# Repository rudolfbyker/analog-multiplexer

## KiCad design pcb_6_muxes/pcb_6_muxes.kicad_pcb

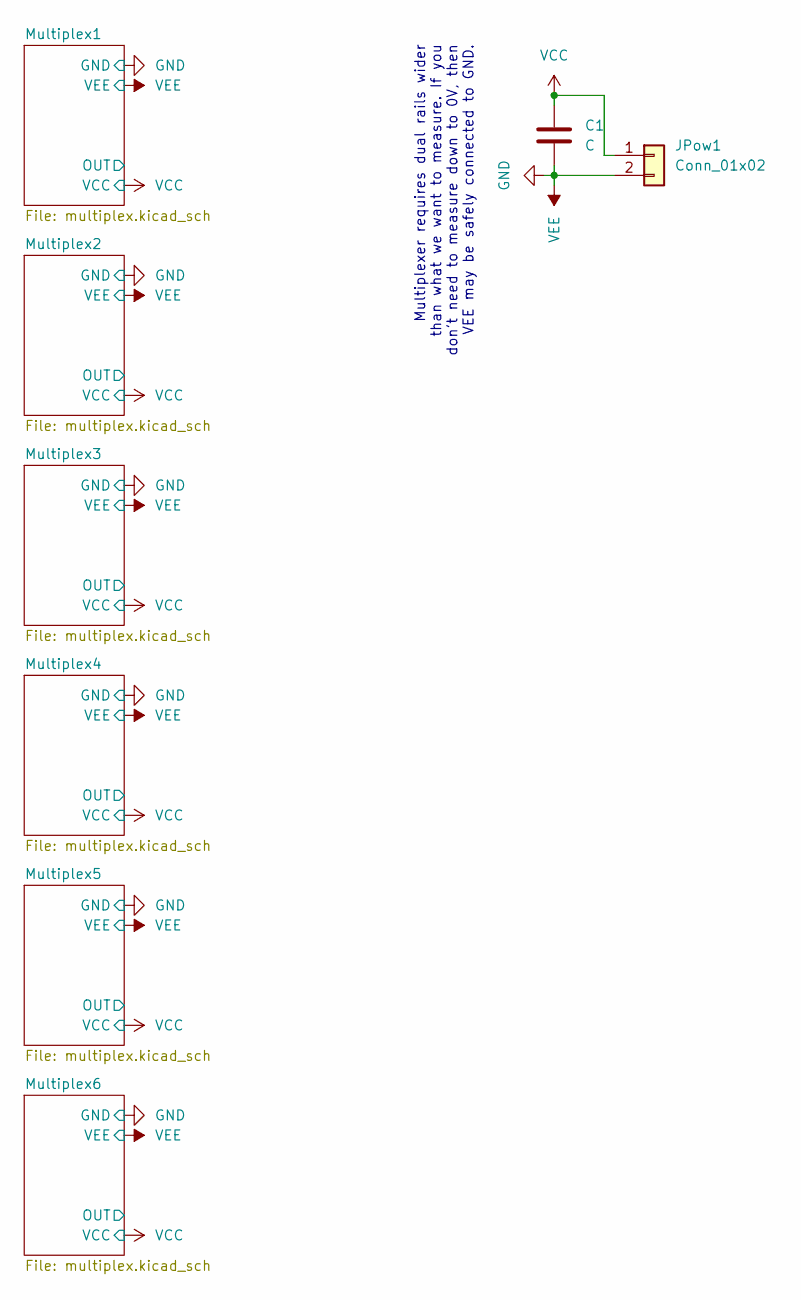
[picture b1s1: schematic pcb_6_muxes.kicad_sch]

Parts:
C1: C; C_Radial_D6.3mm_H5.0mm_P2.50mm
JPow1: Conn_01x02; PinHeader_1x02_P2.54mm_Vertical

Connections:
GND: C1.2, JPow1.2; also elsewhere on the board
VCC: C1.1, JPow1.1; also elsewhere on the board

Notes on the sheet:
Multiplexer requires dual rails wider than what we want to measure. If you don't need to measure down to 0V, then VEE may be safely connected to GND.

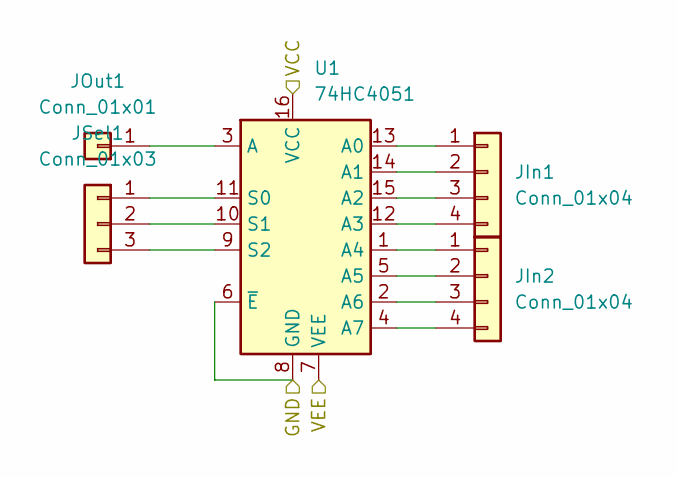
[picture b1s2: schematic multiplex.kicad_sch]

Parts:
JIn1, JIn2: Conn_01x04; PinHeader_1x04_P2.54mm_Vertical
JOut1: Conn_01x01; PinHeader_1x01_P2.54mm_Vertical
JSel1: Conn_01x03; PinHeader_1x03_P2.54mm_Vertical
U1: 74HC4051; DIP-16_W12.7mm_LongPads

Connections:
GND: U1.6 (~E), U1.7 (VEE), U1.8 (GND); also elsewhere on the board
unnamed: JIn1.1, U1.13 (A0)
unnamed: JIn1.2, U1.14 (A1)
unnamed: JIn1.3, U1.15 (A2)
unnamed: JIn1.4, U1.12 (A3)
unnamed: JIn2.1, U1.1 (A4)
unnamed: JIn2.2, U1.5 (A5)
unnamed: JIn2.3, U1.2 (A6)
unnamed: JIn2.4, U1.4 (A7)
unnamed: JOut1.1, U1.3 (A)
unnamed: JSel1.1, U1.11 (S0)
unnamed: JSel1.2, U1.10 (S1)
unnamed: JSel1.3, U1.9 (S2)
VCC: U1.16 (VCC); also elsewhere on the board

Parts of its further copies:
JIn3, JIn4, JIn5, JIn6, JIn7, JIn8, JIn9, JIn10, JIn11, JIn12: Conn_01x04; PinHeader_1x04_P2.54mm_Vertical
JOut2, JOut3, JOut4, JOut5, JOut6: Conn_01x01; PinHeader_1x01_P2.54mm_Vertical
JSel2, JSel3, JSel4, JSel5, JSel6: Conn_01x03; PinHeader_1x03_P2.54mm_Vertical
U2, U3, U4, U5, U6: 74HC4051; DIP-16_W12.7mm_LongPads

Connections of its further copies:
GND: U2.6 (~E), U2.7 (VEE), U2.8 (GND), U3.6 (~E), U3.7 (VEE), U3.8 (GND), U4.6 (~E), U4.7 (VEE), U4.8 (GND), U5.6 (~E), U5.7 (VEE), U5.8 (GND), U6.6 (~E), U6.7 (VEE), U6.8 (GND); also elsewhere on the board
unnamed: JIn3.1, U2.13 (A0)
unnamed: JIn3.2, U2.14 (A1)
unnamed: JIn3.3, U2.15 (A2)
unnamed: JIn3.4, U2.12 (A3)
unnamed: JIn4.1, U2.1 (A4)
unnamed: JIn4.2, U2.5 (A5)
unnamed: JIn4.3, U2.2 (A6)
unnamed: JIn4.4, U2.4 (A7)
unnamed: JIn5.1, U3.13 (A0)
unnamed: JIn5.2, U3.14 (A1)
unnamed: JIn5.3, U3.15 (A2)
unnamed: JIn5.4, U3.12 (A3)
unnamed: JIn6.1, U3.1 (A4)
unnamed: JIn6.2, U3.5 (A5)
unnamed: JIn6.3, U3.2 (A6)
unnamed: JIn6.4, U3.4 (A7)
unnamed: JIn7.1, U4.13 (A0)
unnamed: JIn7.2, U4.14 (A1)
unnamed: JIn7.3, U4.15 (A2)
unnamed: JIn7.4, U4.12 (A3)
unnamed: JIn8.1, U4.1 (A4)
unnamed: JIn8.2, U4.5 (A5)
unnamed: JIn8.3, U4.2 (A6)
unnamed: JIn8.4, U4.4 (A7)
unnamed: JIn9.1, U5.13 (A0)
unnamed: JIn9.2, U5.14 (A1)
unnamed: JIn9.3, U5.15 (A2)
unnamed: JIn9.4, U5.12 (A3)
unnamed: JIn10.1, U5.1 (A4)
unnamed: JIn10.2, U5.5 (A5)
unnamed: JIn10.3, U5.2 (A6)
unnamed: JIn10.4, U5.4 (A7)
unnamed: JIn11.1, U6.13 (A0)
unnamed: JIn11.2, U6.14 (A1)
unnamed: JIn11.3, U6.15 (A2)
unnamed: JIn11.4, U6.12 (A3)
unnamed: JIn12.1, U6.1 (A4)
unnamed: JIn12.2, U6.5 (A5)
unnamed: JIn12.3, U6.2 (A6)
unnamed: JIn12.4, U6.4 (A7)
unnamed: JOut2.1, U2.3 (A)
unnamed: JOut3.1, U3.3 (A)
unnamed: JOut4.1, U4.3 (A)
unnamed: JOut5.1, U5.3 (A)
unnamed: JOut6.1, U6.3 (A)
unnamed: JSel2.1, U2.11 (S0)
unnamed: JSel2.2, U2.10 (S1)
unnamed: JSel2.3, U2.9 (S2)
unnamed: JSel3.1, U3.11 (S0)
unnamed: JSel3.2, U3.10 (S1)
unnamed: JSel3.3, U3.9 (S2)
unnamed: JSel4.1, U4.11 (S0)
unnamed: JSel4.2, U4.10 (S1)
unnamed: JSel4.3, U4.9 (S2)
unnamed: JSel5.1, U5.11 (S0)
unnamed: JSel5.2, U5.10 (S1)
unnamed: JSel5.3, U5.9 (S2)
unnamed: JSel6.1, U6.11 (S0)
unnamed: JSel6.2, U6.10 (S1)
unnamed: JSel6.3, U6.9 (S2)
VCC: U2.16 (VCC), U3.16 (VCC), U4.16 (VCC), U5.16 (VCC), U6.16 (VCC); also elsewhere on the board

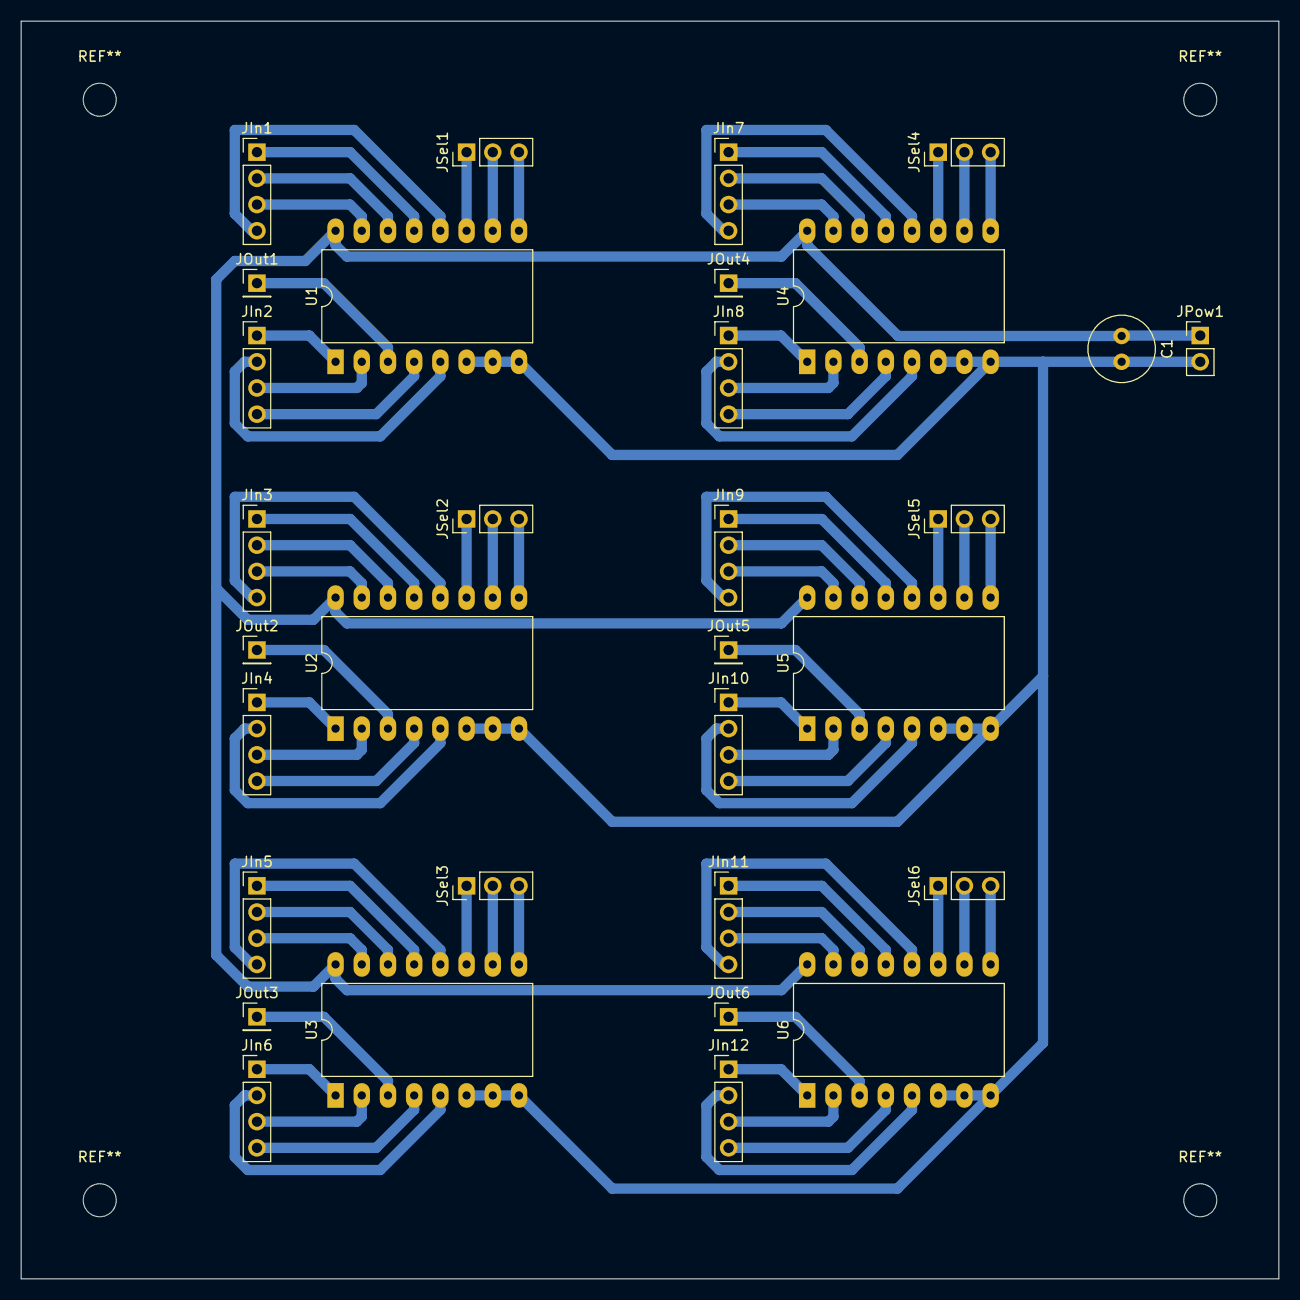
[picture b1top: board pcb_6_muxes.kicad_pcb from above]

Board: 2 copper layers, 121.9 x 121.9 mm, 32 parts (0 on the bottom side), 74 nets.

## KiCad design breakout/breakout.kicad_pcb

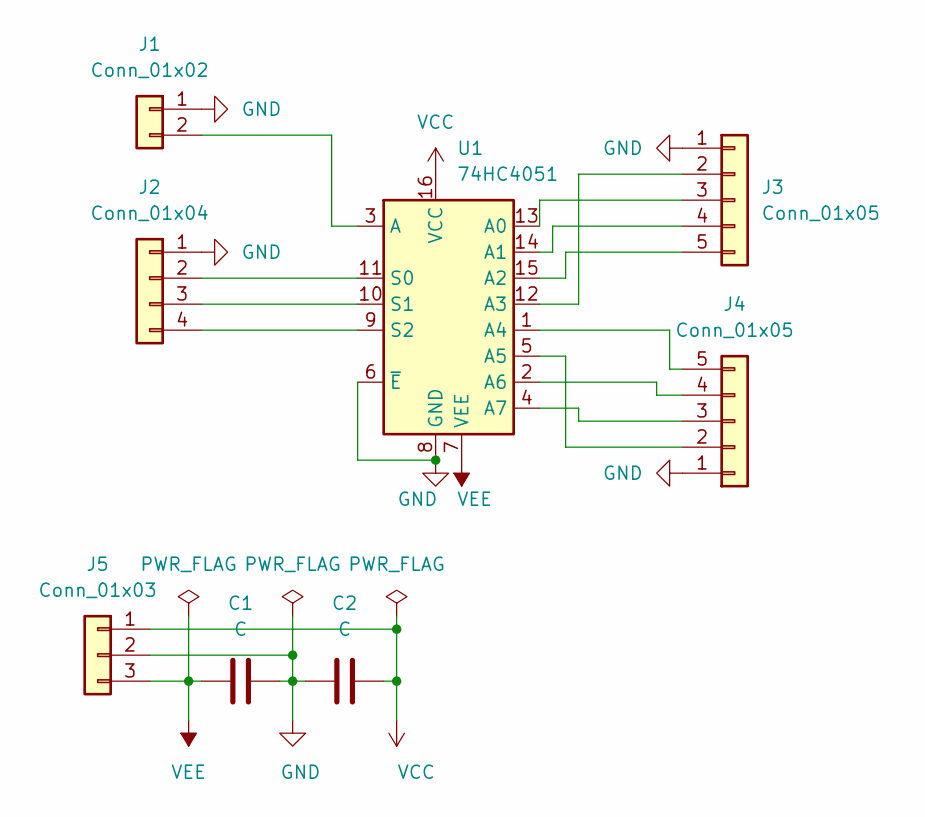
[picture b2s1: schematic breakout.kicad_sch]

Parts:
C1, C2: C; C_0805_2012Metric_Pad1.18x1.45mm_HandSolder
J1: Conn_01x02; PinHeader_1x02_P2.54mm_Vertical
J2: Conn_01x04; PinHeader_1x04_P2.54mm_Vertical
J3, J4: Conn_01x05; PinHeader_1x05_P2.54mm_Vertical
J5: Conn_01x03; PinHeader_1x03_P2.54mm_Vertical
U1: 74HC4051; SO-16_5.3x10.2mm_P1.27mm

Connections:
GND: C1.2, C2.1, J1.1, J2.1, J3.1, J4.1, J5.2, U1.6 (~E), U1.8 (GND)
unnamed: J1.2, U1.3 (A)
unnamed: J2.2, U1.11 (S0)
unnamed: J2.3, U1.10 (S1)
unnamed: J2.4, U1.9 (S2)
unnamed: J3.2, U1.12 (A3)
unnamed: J3.3, U1.13 (A0)
unnamed: J3.4, U1.14 (A1)
unnamed: J3.5, U1.15 (A2)
unnamed: J4.2, U1.5 (A5)
unnamed: J4.3, U1.4 (A7)
unnamed: J4.4, U1.2 (A6)
unnamed: J4.5, U1.1 (A4)
VCC: C2.2, J5.1, U1.16 (VCC)
VEE: C1.1, J5.3, U1.7 (VEE)

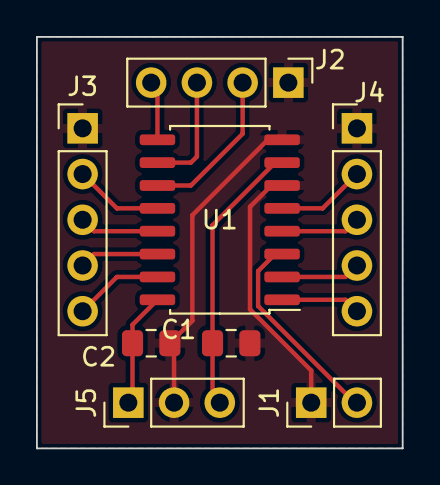
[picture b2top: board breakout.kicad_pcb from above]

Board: 2 copper layers, 20.3 x 22.9 mm, 8 parts (0 on the bottom side), 15 nets.

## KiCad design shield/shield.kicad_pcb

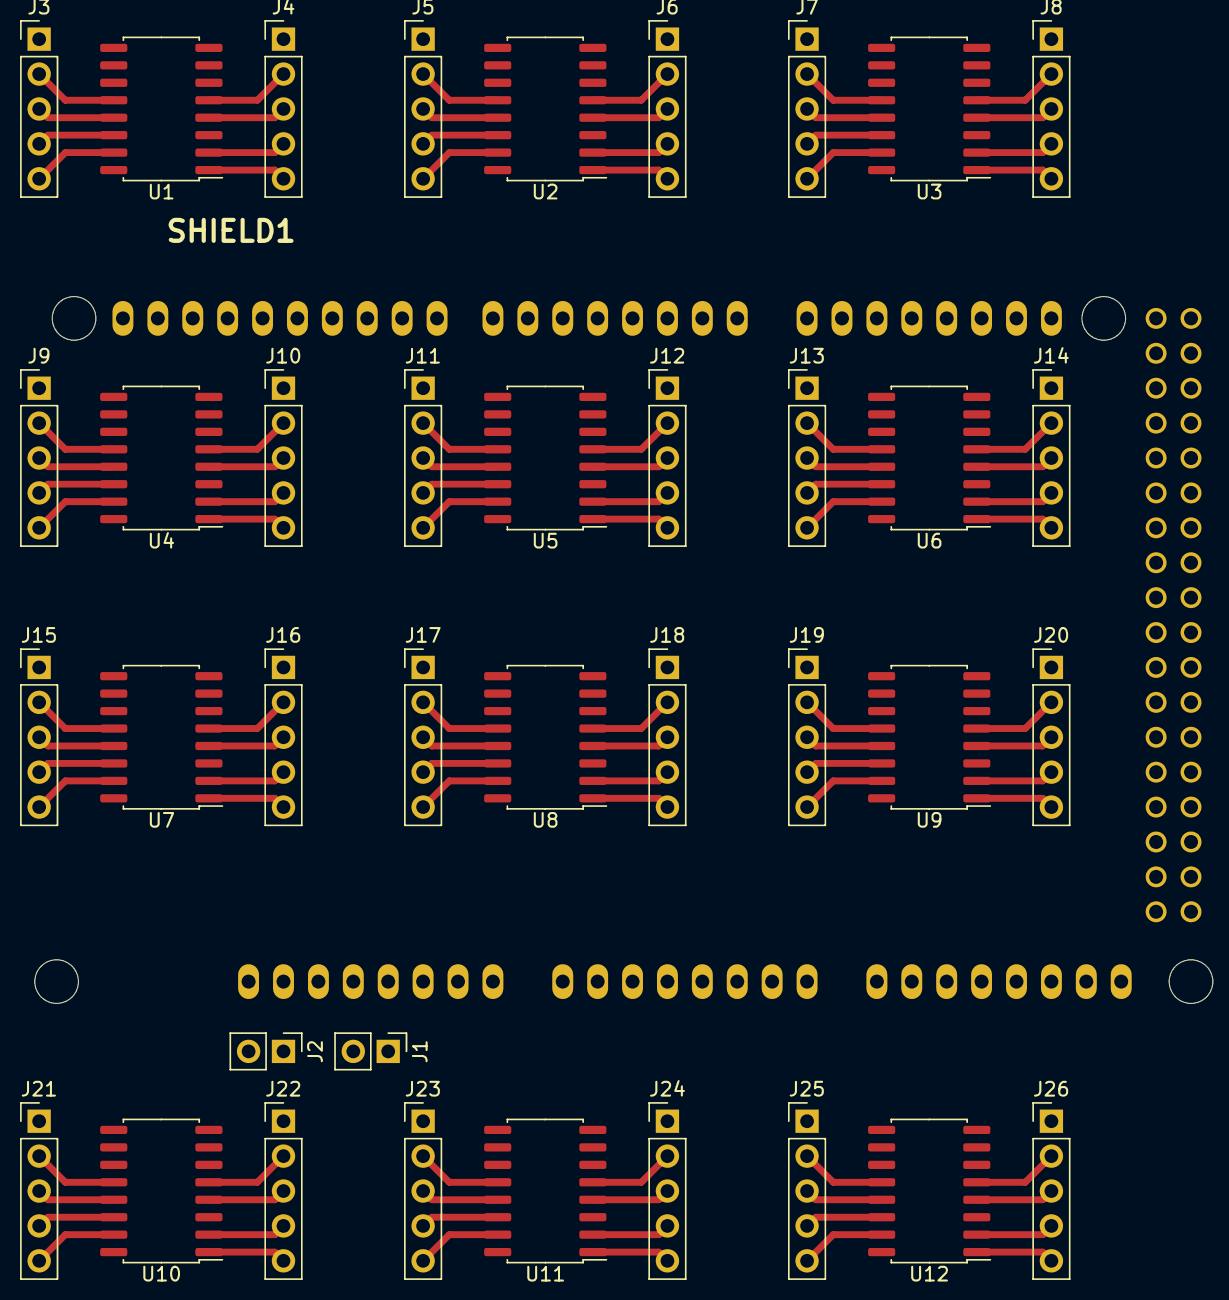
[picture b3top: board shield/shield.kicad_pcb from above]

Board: 2 copper layers, 39 parts (0 on the bottom side), 112 nets.

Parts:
J1, J2: Conn_01x02; PinHeader_1x02_P2.54mm_Vertical
J3, J4, J5, J6, J7, J8, J9, J10, J11, J12, J13, J14, J15, J16, J17, J18, J19, J20, J21, J22, J23, J24, J25, J26: Conn_01x05; PinHeader_1x05_P2.54mm_Vertical
SHIELD1: ARDUINO_DUE_SHIELD
U1, U2, U3, U4, U5, U6, U7, U8, U9, U10, U11, U12: 74HC4051; SO-16_5.3x10.2mm_P1.27mm

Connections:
+3V3: J1.2, SHIELD1.3V3
/A0: SHIELD1.AD0, U1.3 (A)
/A1: SHIELD1.AD1, U2.3 (A)
/A2: SHIELD1.AD2, U3.3 (A)
/A3: SHIELD1.AD3, U4.3 (A)
/A4: SHIELD1.AD4, U5.3 (A)
/A5: SHIELD1.AD5, U6.3 (A)
/A6: SHIELD1.AD6, U7.3 (A)
/A7: SHIELD1.AD7, U8.3 (A)
/A8: SHIELD1.AD8, U9.3 (A)
/A9: SHIELD1.AD9, U10.3 (A)
/A10: SHIELD1.AD10, U11.3 (A)
/A11: SHIELD1.AD11, U12.3 (A)
GND: J1.1, J2.1, J3.1, J4.1, J5.1, J6.1, J7.1, J8.1, J9.1, J10.1, J11.1, J12.1, J13.1, J14.1, J15.1, J16.1, J17.1, J18.1, J19.1, J20.1, J21.1, J22.1, J23.1, J24.1, J25.1, J26.1, SHIELD1.GND1, U1.6 (~E), U1.8 (GND), U2.6 (~E), U2.8 (GND), U3.6 (~E), U3.8 (GND), U4.6 (~E), U4.8 (GND), U5.6 (~E), U5.8 (GND), U6.6 (~E), U6.8 (GND), U7.6 (~E), U7.8 (GND), U8.6 (~E), U8.8 (GND), U9.6 (~E), U9.8 (GND), U10.6 (~E), U10.8 (GND), U11.6 (~E), U11.8 (GND), U12.6 (~E), U12.8 (GND)
unnamed: J4.5, U1.1 (A4)
unnamed: J4.4, U1.2 (A6)
unnamed: J4.3, U1.4 (A7)
unnamed: J4.2, U1.5 (A5)
unnamed: J3.2, U1.12 (A3)
unnamed: J3.3, U1.13 (A0)
unnamed: J3.4, U1.14 (A1)
unnamed: J3.5, U1.15 (A2)
unnamed: J6.5, U2.1 (A4)
unnamed: J6.4, U2.2 (A6)
unnamed: J6.3, U2.4 (A7)
unnamed: J6.2, U2.5 (A5)
unnamed: J5.2, U2.12 (A3)
unnamed: J5.3, U2.13 (A0)
unnamed: J5.4, U2.14 (A1)
unnamed: J5.5, U2.15 (A2)
unnamed: J8.5, U3.1 (A4)
unnamed: J8.4, U3.2 (A6)
unnamed: J8.3, U3.4 (A7)
unnamed: J8.2, U3.5 (A5)
unnamed: J7.2, U3.12 (A3)
unnamed: J7.3, U3.13 (A0)
unnamed: J7.4, U3.14 (A1)
unnamed: J7.5, U3.15 (A2)
unnamed: J10.5, U4.1 (A4)
unnamed: J10.4, U4.2 (A6)
unnamed: J10.3, U4.4 (A7)
unnamed: J10.2, U4.5 (A5)
unnamed: J9.2, U4.12 (A3)
unnamed: J9.3, U4.13 (A0)
unnamed: J9.4, U4.14 (A1)
unnamed: J9.5, U4.15 (A2)
unnamed: J12.5, U5.1 (A4)
unnamed: J12.4, U5.2 (A6)
unnamed: J12.3, U5.4 (A7)
unnamed: J12.2, U5.5 (A5)
unnamed: J11.2, U5.12 (A3)
unnamed: J11.3, U5.13 (A0)
unnamed: J11.4, U5.14 (A1)
unnamed: J11.5, U5.15 (A2)
unnamed: J14.5, U6.1 (A4)
unnamed: J14.4, U6.2 (A6)
unnamed: J14.3, U6.4 (A7)
unnamed: J14.2, U6.5 (A5)
unnamed: J13.2, U6.12 (A3)
unnamed: J13.3, U6.13 (A0)
unnamed: J13.4, U6.14 (A1)
unnamed: J13.5, U6.15 (A2)
unnamed: J16.5, U7.1 (A4)
unnamed: J16.4, U7.2 (A6)
unnamed: J16.3, U7.4 (A7)
unnamed: J16.2, U7.5 (A5)
unnamed: J15.2, U7.12 (A3)
unnamed: J15.3, U7.13 (A0)
unnamed: J15.4, U7.14 (A1)
unnamed: J15.5, U7.15 (A2)
unnamed: J18.5, U8.1 (A4)
unnamed: J18.4, U8.2 (A6)
unnamed: J18.3, U8.4 (A7)
unnamed: J18.2, U8.5 (A5)
unnamed: J17.2, U8.12 (A3)
unnamed: J17.3, U8.13 (A0)
unnamed: J17.4, U8.14 (A1)
unnamed: J17.5, U8.15 (A2)
unnamed: J20.5, U9.1 (A4)
unnamed: J20.4, U9.2 (A6)
unnamed: J20.3, U9.4 (A7)
unnamed: J20.2, U9.5 (A5)
unnamed: J19.2, U9.12 (A3)
unnamed: J19.3, U9.13 (A0)
unnamed: J19.4, U9.14 (A1)
unnamed: J19.5, U9.15 (A2)
unnamed: J22.5, U10.1 (A4)
unnamed: J22.4, U10.2 (A6)
unnamed: J22.3, U10.4 (A7)
unnamed: J22.2, U10.5 (A5)
unnamed: J21.2, U10.12 (A3)
unnamed: J21.3, U10.13 (A0)
unnamed: J21.4, U10.14 (A1)
unnamed: J21.5, U10.15 (A2)
unnamed: J24.5, U11.1 (A4)
unnamed: J24.4, U11.2 (A6)
unnamed: J24.3, U11.4 (A7)
unnamed: J24.2, U11.5 (A5)
unnamed: J23.2, U11.12 (A3)
unnamed: J23.3, U11.13 (A0)
unnamed: J23.4, U11.14 (A1)
unnamed: J23.5, U11.15 (A2)
unnamed: J26.5, U12.1 (A4)
unnamed: J26.4, U12.2 (A6)
unnamed: J26.3, U12.4 (A7)
unnamed: J26.2, U12.5 (A5)
unnamed: J25.2, U12.12 (A3)
unnamed: J25.3, U12.13 (A0)
unnamed: J25.4, U12.14 (A1)
unnamed: J25.5, U12.15 (A2)
VCC: SHIELD1.5V, U1.16 (VCC), U2.16 (VCC), U3.16 (VCC), U4.16 (VCC), U5.16 (VCC), U6.16 (VCC), U7.16 (VCC), U8.16 (VCC), U9.16 (VCC), U10.16 (VCC), U11.16 (VCC), U12.16 (VCC)
VEE: J2.2, U1.7 (VEE), U2.7 (VEE), U3.7 (VEE), U4.7 (VEE), U5.7 (VEE), U6.7 (VEE), U7.7 (VEE), U8.7 (VEE), U9.7 (VEE), U10.7 (VEE), U11.7 (VEE), U12.7 (VEE)

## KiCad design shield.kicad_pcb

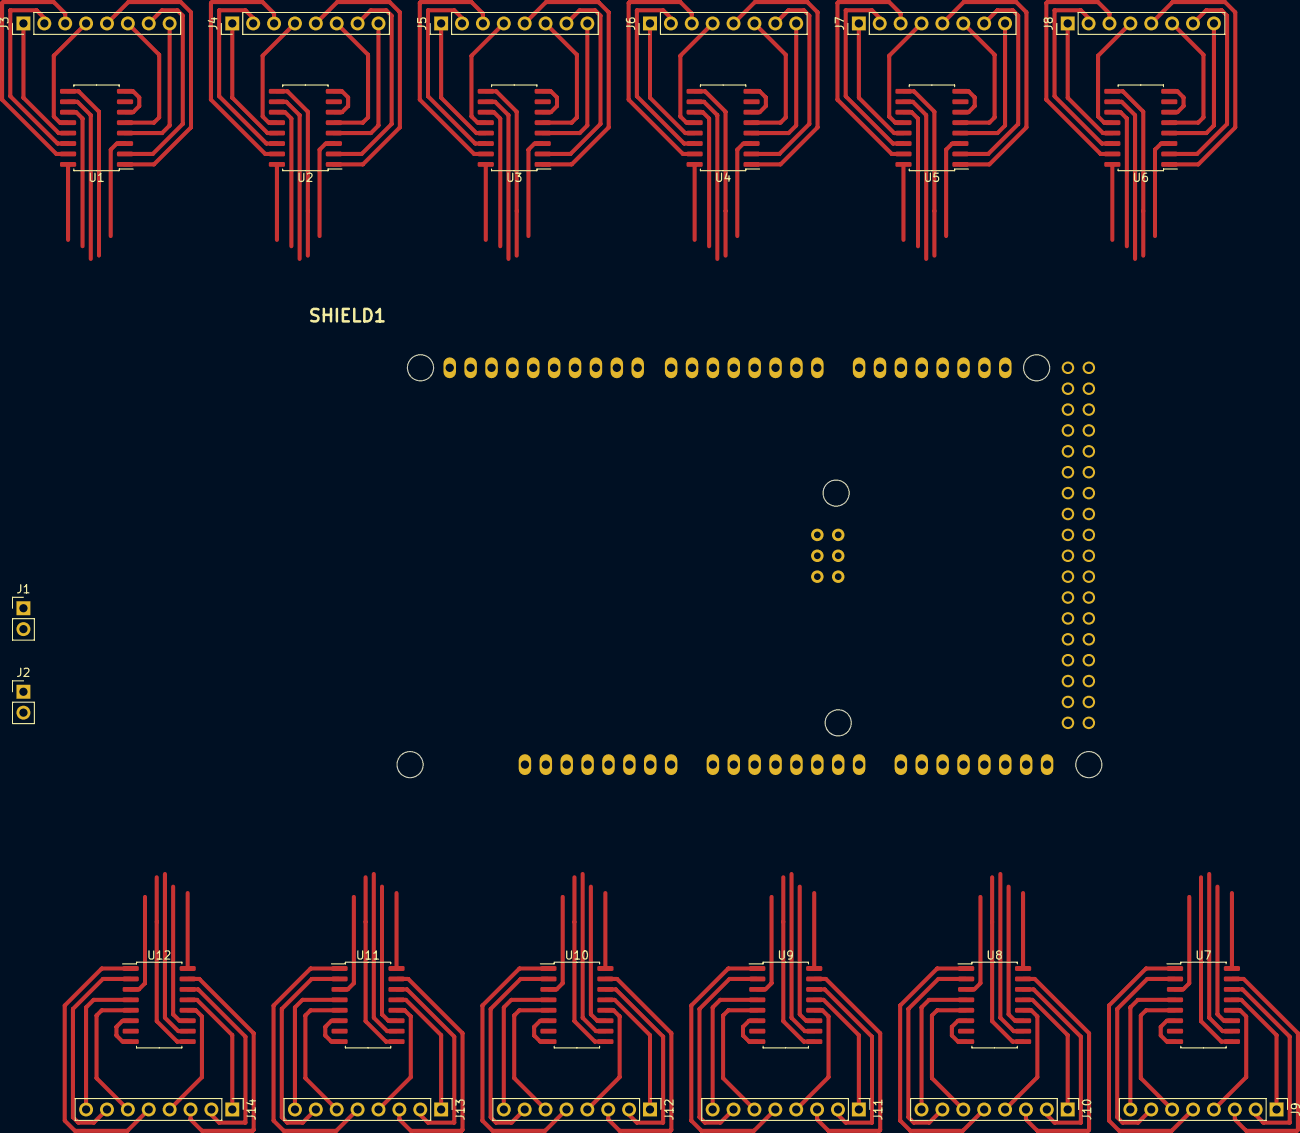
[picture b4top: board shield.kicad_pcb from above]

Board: 2 copper layers, 27 parts (0 on the bottom side), 112 nets.

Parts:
J1, J2: Conn_01x02; PinHeader_1x02_P2.54mm_Vertical
J3, J4, J5, J6, J7, J8, J9, J10, J11, J12, J13, J14: Conn_01x08; PinHeader_1x08_P2.54mm_Vertical
SHIELD1: ARDUINO_DUE_SHIELD
U1, U2, U3, U4, U5, U6, U7, U8, U9, U10, U11, U12: 74HC4051; SO-16_5.3x10.2mm_P1.27mm

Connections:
+3V3: J1.2, SHIELD1.3V3
/A0: SHIELD1.AD0, U1.3 (A)
/A1: SHIELD1.AD1, U2.3 (A)
/A2: SHIELD1.AD2, U3.3 (A)
/A3: SHIELD1.AD3, U4.3 (A)
/A4: SHIELD1.AD4, U5.3 (A)
/A5: SHIELD1.AD5, U6.3 (A)
/A6: SHIELD1.AD6, U7.3 (A)
/A7: SHIELD1.AD7, U8.3 (A)
/A8: SHIELD1.AD8, U9.3 (A)
/A9: SHIELD1.AD9, U10.3 (A)
/A10: SHIELD1.AD10, U11.3 (A)
/A11: SHIELD1.AD11, U12.3 (A)
GND: J1.1, J2.1, SHIELD1.GND1, U1.6 (~E), U1.8 (GND), U2.6 (~E), U2.8 (GND), U3.6 (~E), U3.8 (GND), U4.6 (~E), U4.8 (GND), U5.6 (~E), U5.8 (GND), U6.6 (~E), U6.8 (GND), U7.6 (~E), U7.8 (GND), U8.6 (~E), U8.8 (GND), U9.6 (~E), U9.8 (GND), U10.6 (~E), U10.8 (GND), U11.6 (~E), U11.8 (GND), U12.6 (~E), U12.8 (GND)
unnamed: J3.1, U1.13 (A0)
unnamed: J3.2, U1.14 (A1)
unnamed: J3.3, U1.15 (A2)
unnamed: J3.4, U1.12 (A3)
unnamed: J3.5, U1.1 (A4)
unnamed: J3.6, U1.5 (A5)
unnamed: J3.7, U1.2 (A6)
unnamed: J3.8, U1.4 (A7)
unnamed: J4.1, U2.13 (A0)
unnamed: J4.2, U2.14 (A1)
unnamed: J4.3, U2.15 (A2)
unnamed: J4.4, U2.12 (A3)
unnamed: J4.5, U2.1 (A4)
unnamed: J4.6, U2.5 (A5)
unnamed: J4.7, U2.2 (A6)
unnamed: J4.8, U2.4 (A7)
unnamed: J5.1, U3.13 (A0)
unnamed: J5.2, U3.14 (A1)
unnamed: J5.3, U3.15 (A2)
unnamed: J5.4, U3.12 (A3)
unnamed: J5.5, U3.1 (A4)
unnamed: J5.6, U3.5 (A5)
unnamed: J5.7, U3.2 (A6)
unnamed: J5.8, U3.4 (A7)
unnamed: J6.1, U4.13 (A0)
unnamed: J6.2, U4.14 (A1)
unnamed: J6.3, U4.15 (A2)
unnamed: J6.4, U4.12 (A3)
unnamed: J6.5, U4.1 (A4)
unnamed: J6.6, U4.5 (A5)
unnamed: J6.7, U4.2 (A6)
unnamed: J6.8, U4.4 (A7)
unnamed: J7.1, U5.13 (A0)
unnamed: J7.2, U5.14 (A1)
unnamed: J7.3, U5.15 (A2)
unnamed: J7.4, U5.12 (A3)
unnamed: J7.5, U5.1 (A4)
unnamed: J7.6, U5.5 (A5)
unnamed: J7.7, U5.2 (A6)
unnamed: J7.8, U5.4 (A7)
unnamed: J8.1, U6.13 (A0)
unnamed: J8.2, U6.14 (A1)
unnamed: J8.3, U6.15 (A2)
unnamed: J8.4, U6.12 (A3)
unnamed: J8.5, U6.1 (A4)
unnamed: J8.6, U6.5 (A5)
unnamed: J8.7, U6.2 (A6)
unnamed: J8.8, U6.4 (A7)
unnamed: J9.1, U7.13 (A0)
unnamed: J9.2, U7.14 (A1)
unnamed: J9.3, U7.15 (A2)
unnamed: J9.4, U7.12 (A3)
unnamed: J9.5, U7.1 (A4)
unnamed: J9.6, U7.5 (A5)
unnamed: J9.7, U7.2 (A6)
unnamed: J9.8, U7.4 (A7)
unnamed: J10.1, U8.13 (A0)
unnamed: J10.2, U8.14 (A1)
unnamed: J10.3, U8.15 (A2)
unnamed: J10.4, U8.12 (A3)
unnamed: J10.5, U8.1 (A4)
unnamed: J10.6, U8.5 (A5)
unnamed: J10.7, U8.2 (A6)
unnamed: J10.8, U8.4 (A7)
unnamed: J11.1, U9.13 (A0)
unnamed: J11.2, U9.14 (A1)
unnamed: J11.3, U9.15 (A2)
unnamed: J11.4, U9.12 (A3)
unnamed: J11.5, U9.1 (A4)
unnamed: J11.6, U9.5 (A5)
unnamed: J11.7, U9.2 (A6)
unnamed: J11.8, U9.4 (A7)
unnamed: J12.1, U10.13 (A0)
unnamed: J12.2, U10.14 (A1)
unnamed: J12.3, U10.15 (A2)
unnamed: J12.4, U10.12 (A3)
unnamed: J12.5, U10.1 (A4)
unnamed: J12.6, U10.5 (A5)
unnamed: J12.7, U10.2 (A6)
unnamed: J12.8, U10.4 (A7)
unnamed: J13.1, U11.13 (A0)
unnamed: J13.2, U11.14 (A1)
unnamed: J13.3, U11.15 (A2)
unnamed: J13.4, U11.12 (A3)
unnamed: J13.5, U11.1 (A4)
unnamed: J13.6, U11.5 (A5)
unnamed: J13.7, U11.2 (A6)
unnamed: J13.8, U11.4 (A7)
unnamed: J14.1, U12.13 (A0)
unnamed: J14.2, U12.14 (A1)
unnamed: J14.3, U12.15 (A2)
unnamed: J14.4, U12.12 (A3)
unnamed: J14.5, U12.1 (A4)
unnamed: J14.6, U12.5 (A5)
unnamed: J14.7, U12.2 (A6)
unnamed: J14.8, U12.4 (A7)
VCC: SHIELD1.5V, U1.16 (VCC), U2.16 (VCC), U3.16 (VCC), U4.16 (VCC), U5.16 (VCC), U6.16 (VCC), U7.16 (VCC), U8.16 (VCC), U9.16 (VCC), U10.16 (VCC), U11.16 (VCC), U12.16 (VCC)
VEE: J2.2, U1.7 (VEE), U2.7 (VEE), U3.7 (VEE), U4.7 (VEE), U5.7 (VEE), U6.7 (VEE), U7.7 (VEE), U8.7 (VEE), U9.7 (VEE), U10.7 (VEE), U11.7 (VEE), U12.7 (VEE)

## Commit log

2022-05-25 Add MIT license
2022-05-25 Move incomplete shield to separate dir, and add complete breakout design for a single multiplexer.
2022-05-26 Add 0805 decoupling capacitor pads to the breakout board.
2023-05-01 Add .editorconfig
2023-05-01 Add .gitattributes
2023-05-01 Add Arduino example code.
2023-05-01 Add multiplexer datasheet.
2023-05-01 Some unknown changes that were lying around.
2023-05-01 Add Flatcam project
2023-06-17 Unknown
2023-06-17 Add PCB with 6 multiplexers
2023-06-17 Re-layout with VEE=GND on 121mmx121mm single sided board.
2023-06-17 Output fabrication files
2023-06-25 Move copper from top to bottom layer for easier solering on single sided board.
2023-06-25 Change drill file to metric units. Export edge cuts. Disable X2 format.
2023-06-25 Fix fab origin
2023-06-25 Make GCode using FlatCAM 8.5
2023-06-25 Fix feed rates
2023-06-25 Manually edit gcode to remove isolation routing from the outside of the PCB (it cuts our masking tape and wastes time)
2023-06-25 Make single-pass isolation gcode
